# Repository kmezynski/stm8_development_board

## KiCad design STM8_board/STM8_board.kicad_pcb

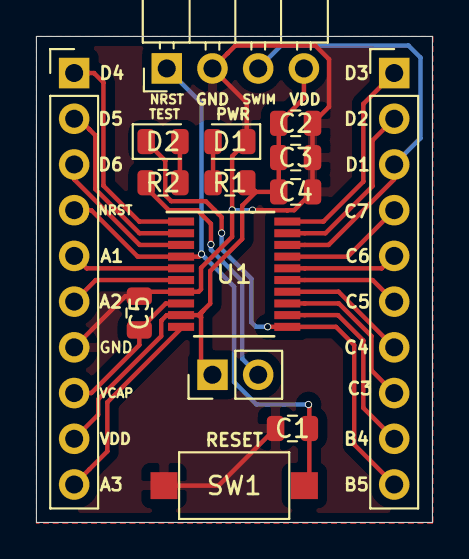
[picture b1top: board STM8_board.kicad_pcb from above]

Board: 2 copper layers, 22.0 x 27.0 mm, 15 parts (0 on the bottom side), 23 nets.

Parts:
C1: 1nF; C_0805_2012Metric
C2: 100n; C_0805_2012Metric
C3, C5: 1u; C_0805_2012Metric
C4: 10u; C_0805_2012Metric
D1, D2: LED; LED_0805_2012Metric
J1, J2: Conn_01x10; PinHeader_1x10_P2.54mm_Vertical
J3: Conn_01x04; PinHeader_1x04_P2.54mm_Horizontal
J4: Conn_01x02; PinHeader_1x02_P2.54mm_Vertical
R1, R2: 1k; R_0805_2012Metric
SW1: SW_Push; SW_SPST_CK_RS282G05A3
U1: STM8S003F3P; TSSOP-20_4.4x6.5mm_P0.65mm

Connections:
GND: C1.2, C2.2, C3.2, C4.2, C5.2, D1.1, J1.7, J3.2, SW1.2, U1.7
NRST: C1.1, J1.4, J3.1, SW1.1, U1.4
unnamed: D1.2, R1.2
unnamed: D2.2, R2.2
unnamed: J4.2, R2.1
PA1: J1.5, U1.5
PA2: J1.6, U1.6
PA3: J1.10, U1.10
PB4: J2.9, U1.12
PB5: D2.1, J2.10, U1.11
PC3: J2.8, U1.13
PC4: J2.7, U1.14
PC5: J2.6, U1.15
PC6: J2.5, U1.16
PC7: J2.4, U1.17
PD1: J2.3, J3.3, U1.18
PD2: J2.2, U1.19
PD3: J2.1, U1.20
PD4: J1.1, U1.1
PD5: J1.2, U1.2
PD6: J1.3, U1.3
VCAP: C5.1, J1.8, U1.8
VDD: C2.1, C3.1, C4.1, J1.9, J3.4, J4.1, R1.1, U1.9

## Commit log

2020-05-14 STM8S datasheets
2020-05-14 PTS636 datasheet
2020-05-14 pcb layout
2020-05-14 pcb logo
2020-05-14 pcb schematics
2020-05-14 STM8 board final version
2020-05-14 STM8 board gerber files
2020-05-21 update LICENSE
